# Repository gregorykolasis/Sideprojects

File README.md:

# Sideprojects
Some Python/Bat scripts for doing CD/CI operations , or scripts helping in deployment or general use scripts

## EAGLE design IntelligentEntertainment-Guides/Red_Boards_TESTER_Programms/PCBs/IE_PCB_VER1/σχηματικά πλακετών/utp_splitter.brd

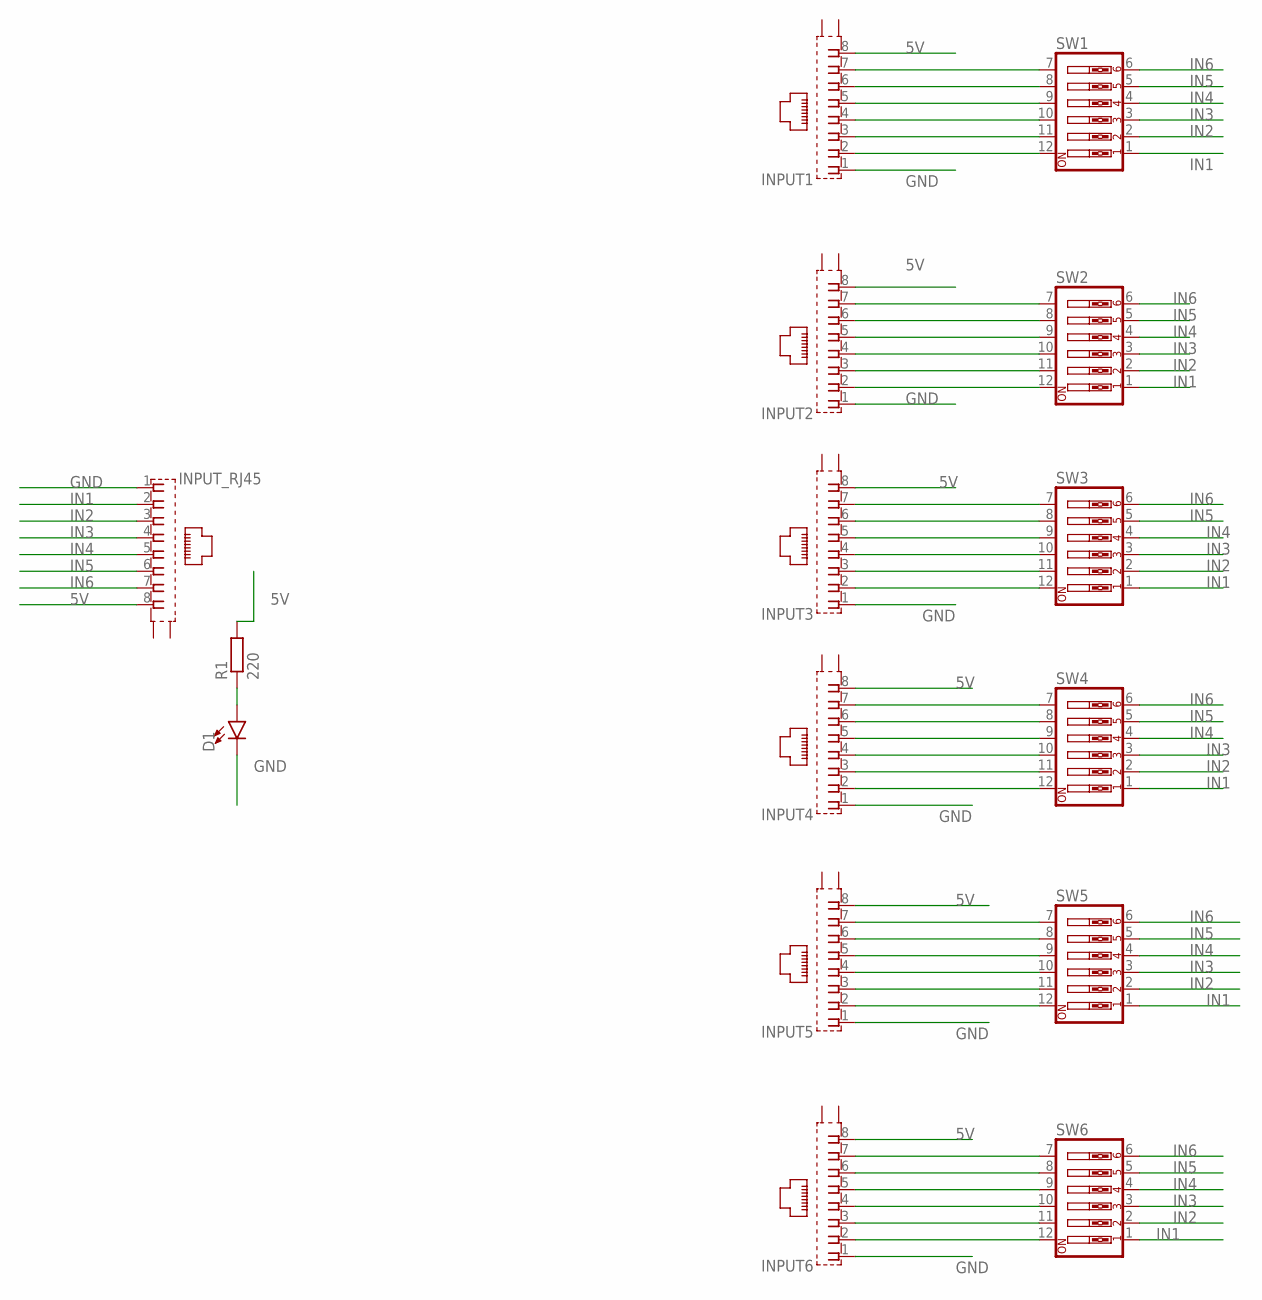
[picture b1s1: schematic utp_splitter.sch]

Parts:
D1: LED-5MM-KIT-NO-SILK; LED_5MM-KIT-NO-SILK
INPUT1, INPUT2, INPUT3, INPUT4, INPUT5, INPUT6: GLX-S-88M
INPUT_RJ45: GLX-S-88M
R1: 220; 0207/10
SW1, SW2, SW3, SW4, SW5, SW6: SW_DIP-6; EDG-06

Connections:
5V: INPUT1.8, INPUT2.8, INPUT3.8, INPUT4.8, INPUT5.8, INPUT6.8, INPUT_RJ45.8, R1.2
GND: D1.K (C), INPUT1.1, INPUT2.1, INPUT3.1, INPUT4.1, INPUT5.1, INPUT6.1, INPUT_RJ45.1
IN1: INPUT_RJ45.2, SW1.1, SW2.1, SW3.1, SW4.1, SW5.1, SW6.1
IN2: INPUT_RJ45.3, SW1.2, SW2.2, SW3.2, SW4.2, SW5.2, SW6.2
IN3: INPUT_RJ45.4, SW1.3, SW2.3, SW3.3, SW4.3, SW5.3, SW6.3
IN4: INPUT_RJ45.5, SW1.4, SW2.4, SW3.4, SW4.4, SW5.4, SW6.4
IN5: INPUT_RJ45.6, SW1.5, SW2.5, SW3.5, SW4.5, SW5.5, SW6.5
IN6: INPUT_RJ45.7, SW1.6, SW2.6, SW3.6, SW4.6, SW5.6, SW6.6
unnamed: INPUT6.7, SW6.7
unnamed: INPUT6.6, SW6.8
unnamed: INPUT6.5, SW6.9
unnamed: INPUT6.4, SW6.10
unnamed: INPUT6.3, SW6.11
unnamed: INPUT6.2, SW6.12
unnamed: D1.A, R1.1
unnamed: INPUT1.7, SW1.7
unnamed: INPUT1.6, SW1.8
unnamed: INPUT1.5, SW1.9
unnamed: INPUT1.4, SW1.10
unnamed: INPUT1.3, SW1.11
unnamed: INPUT1.2, SW1.12
unnamed: INPUT2.7, SW2.7
unnamed: INPUT2.6, SW2.8
unnamed: INPUT2.5, SW2.9
unnamed: INPUT2.4, SW2.10
unnamed: INPUT2.3, SW2.11
unnamed: INPUT2.2, SW2.12
unnamed: INPUT3.7, SW3.7
unnamed: INPUT3.6, SW3.8
unnamed: INPUT3.5, SW3.9
unnamed: INPUT3.4, SW3.10
unnamed: INPUT3.3, SW3.11
unnamed: INPUT3.2, SW3.12
unnamed: INPUT4.7, SW4.7
unnamed: INPUT4.6, SW4.8
unnamed: INPUT4.5, SW4.9
unnamed: INPUT4.4, SW4.10
unnamed: INPUT4.3, SW4.11
unnamed: INPUT4.2, SW4.12
unnamed: INPUT5.7, SW5.7
unnamed: INPUT5.6, SW5.8
unnamed: INPUT5.5, SW5.9
unnamed: INPUT5.4, SW5.10
unnamed: INPUT5.3, SW5.11
unnamed: INPUT5.2, SW5.12

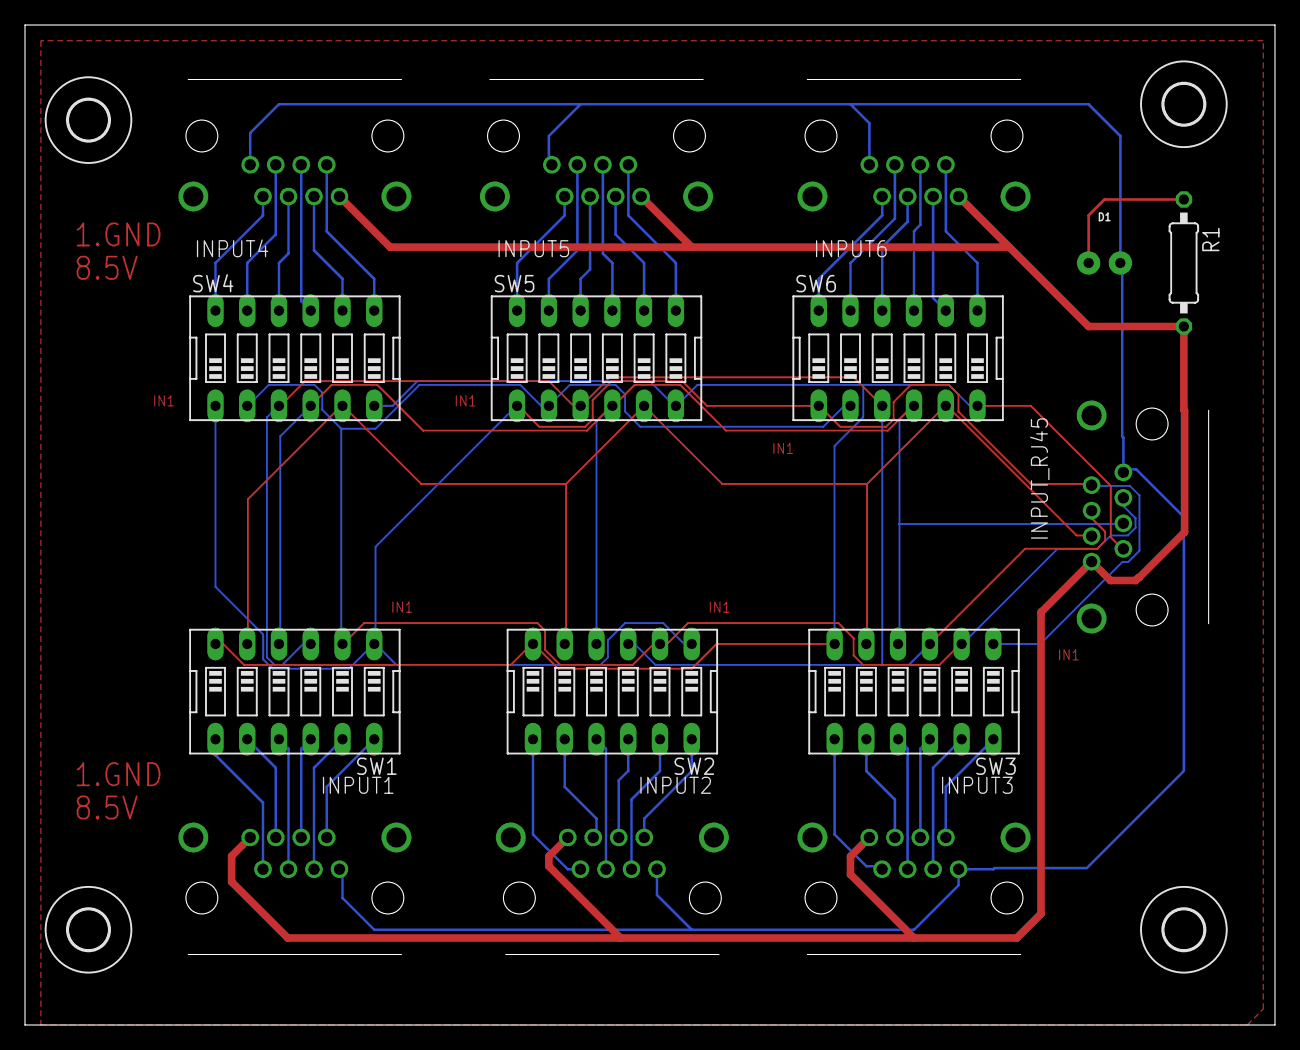
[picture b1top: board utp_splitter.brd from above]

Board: 2 copper layers, 100.0 x 80.0 mm, 19 parts (0 on the bottom side), 45 nets.

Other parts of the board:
U$1, U$2, U$3, U$4: 3,2

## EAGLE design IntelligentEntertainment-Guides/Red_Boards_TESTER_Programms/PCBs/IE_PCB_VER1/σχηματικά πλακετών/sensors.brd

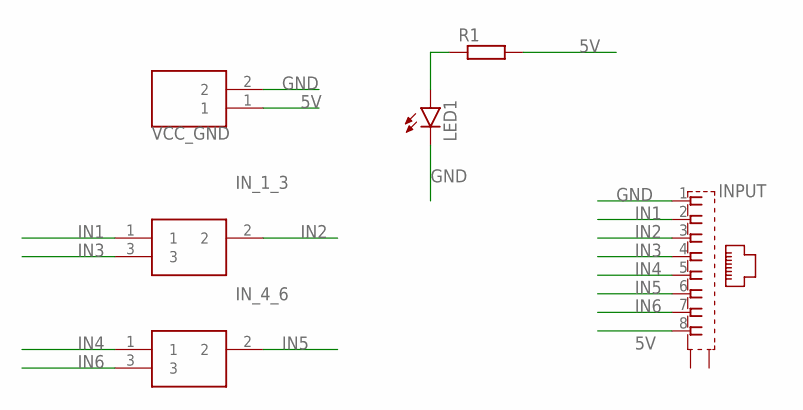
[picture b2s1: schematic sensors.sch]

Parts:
INPUT: GLX-S-88M
IN_1_3, IN_4_6: SAMACSYS_PARTS_TB006-508-03BE; SAMACSYS_PARTS_TB00650803BE
LED1: LED5MM
R1: R-EU_0207/10; 0207/10
VCC_GND: TB006-508-02BE_TB006-508-02BE; TB006-508-02BE_CUI_TB006-508-02BE

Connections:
5V: INPUT.8, R1.2, VCC_GND.1
GND: INPUT.1, LED1.K (C), VCC_GND.2
IN1: INPUT.2, IN_1_3.1
IN2: INPUT.3, IN_1_3.2
IN3: INPUT.4, IN_1_3.3
IN4: INPUT.5, IN_4_6.1
IN5: INPUT.6, IN_4_6.2
IN6: INPUT.7, IN_4_6.3
unnamed: LED1.A, R1.1

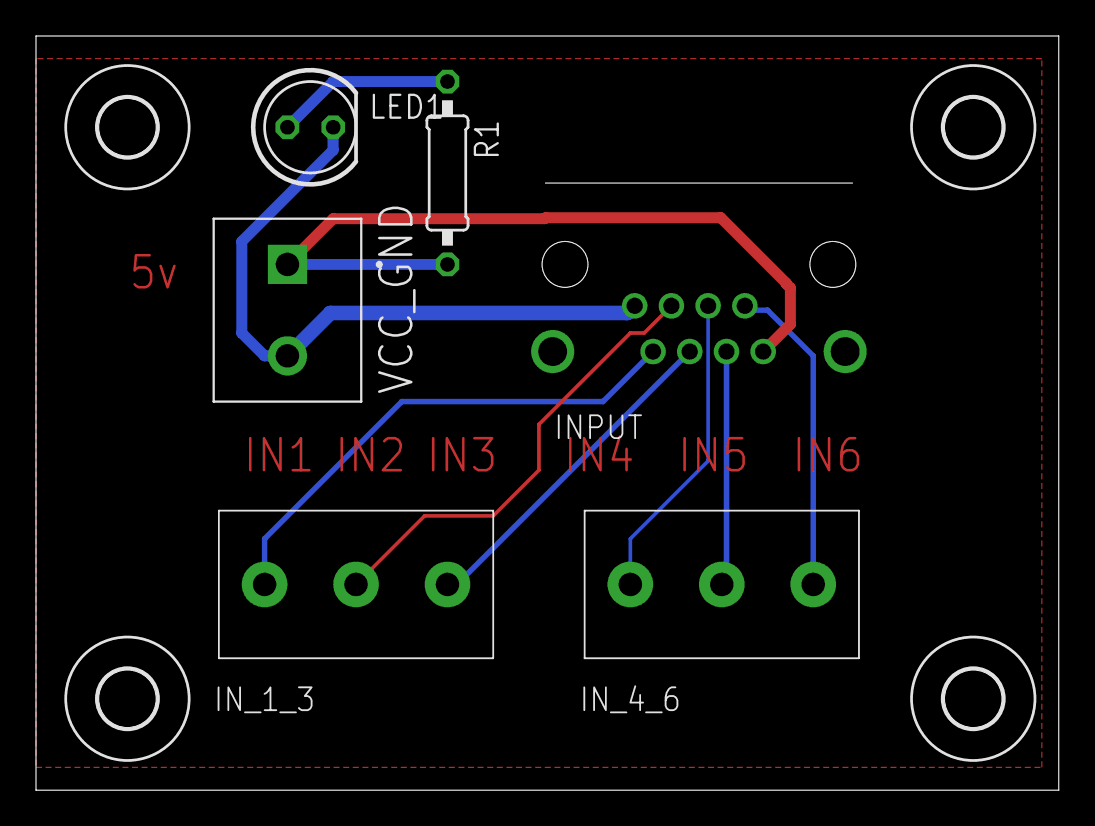
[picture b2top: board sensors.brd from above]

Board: 2 copper layers, 56.8 x 41.9 mm, 10 parts (0 on the bottom side), 9 nets.

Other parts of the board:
U$1, U$2, U$3, U$4: 3,2

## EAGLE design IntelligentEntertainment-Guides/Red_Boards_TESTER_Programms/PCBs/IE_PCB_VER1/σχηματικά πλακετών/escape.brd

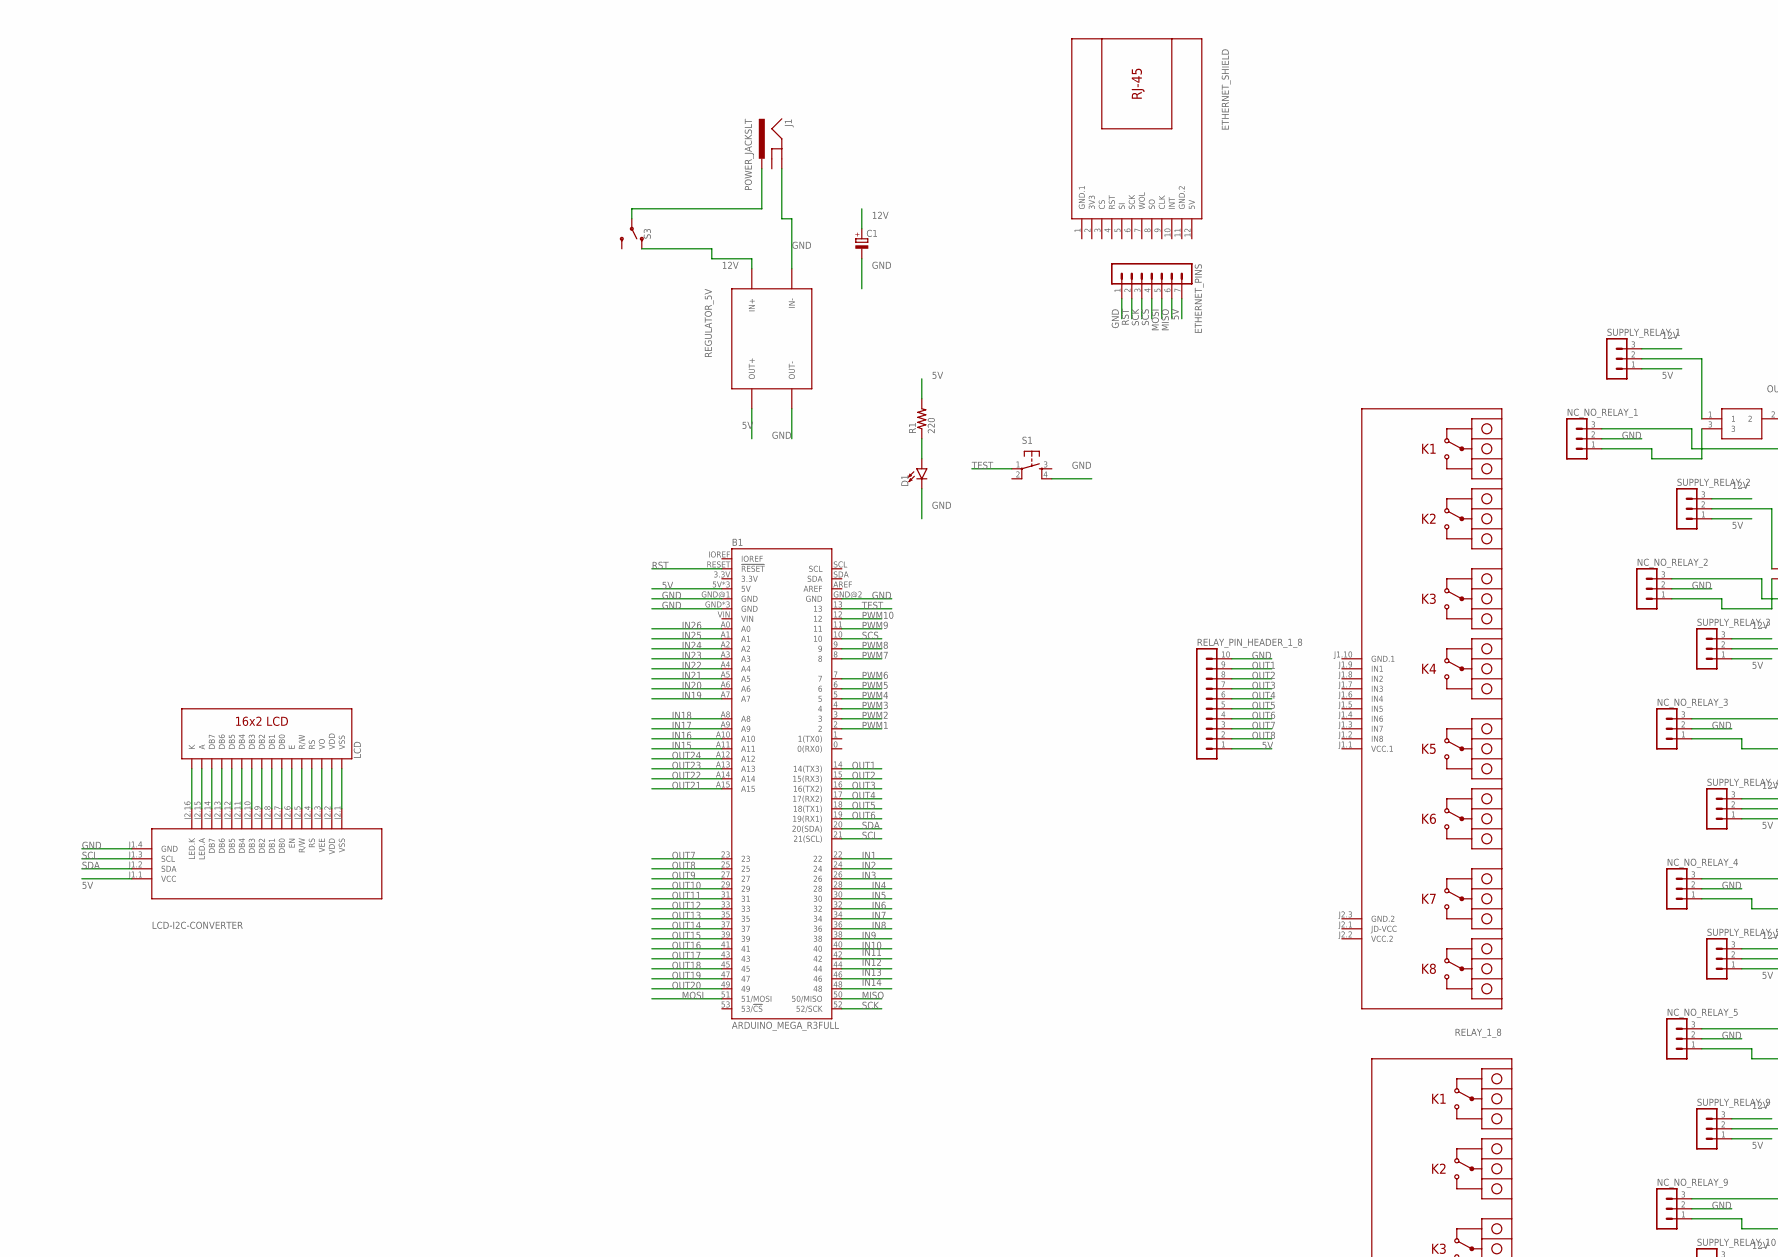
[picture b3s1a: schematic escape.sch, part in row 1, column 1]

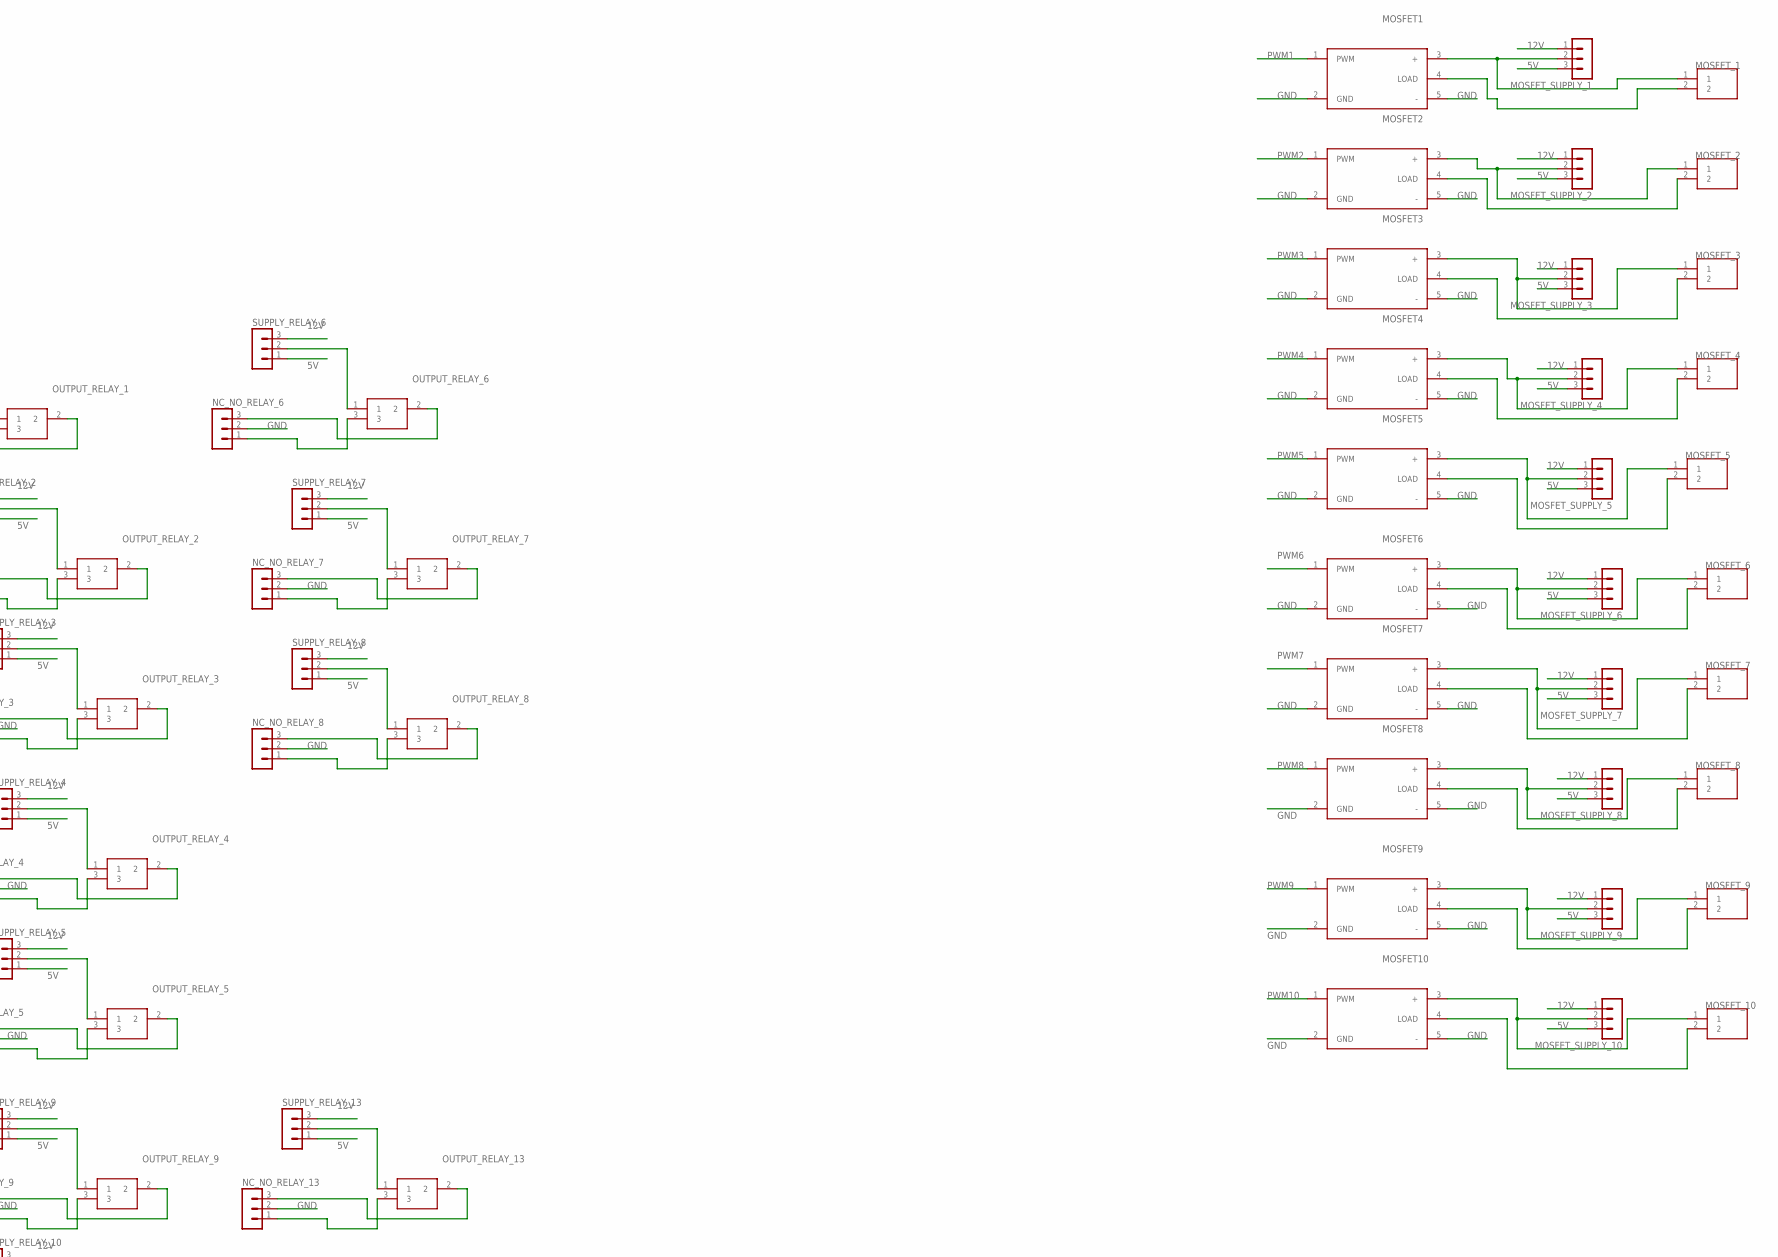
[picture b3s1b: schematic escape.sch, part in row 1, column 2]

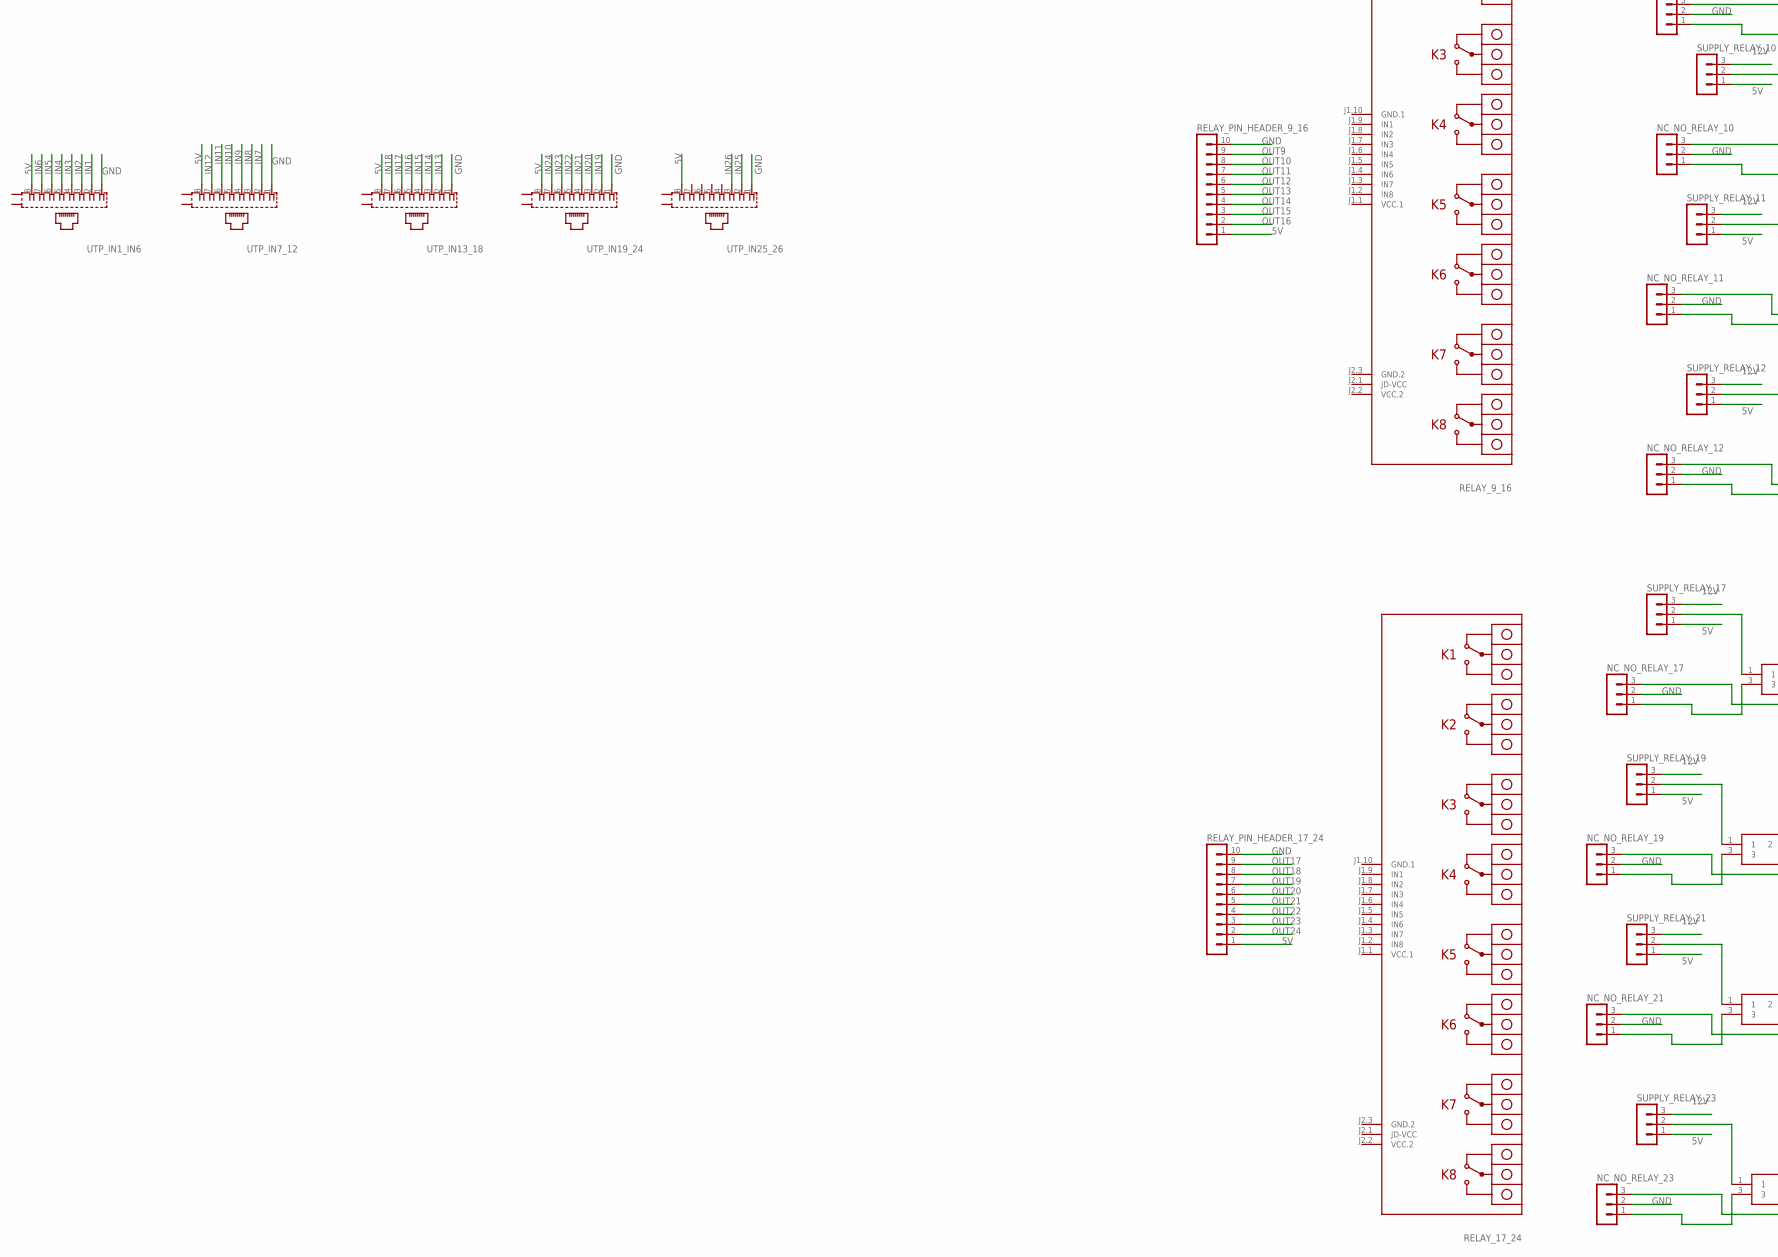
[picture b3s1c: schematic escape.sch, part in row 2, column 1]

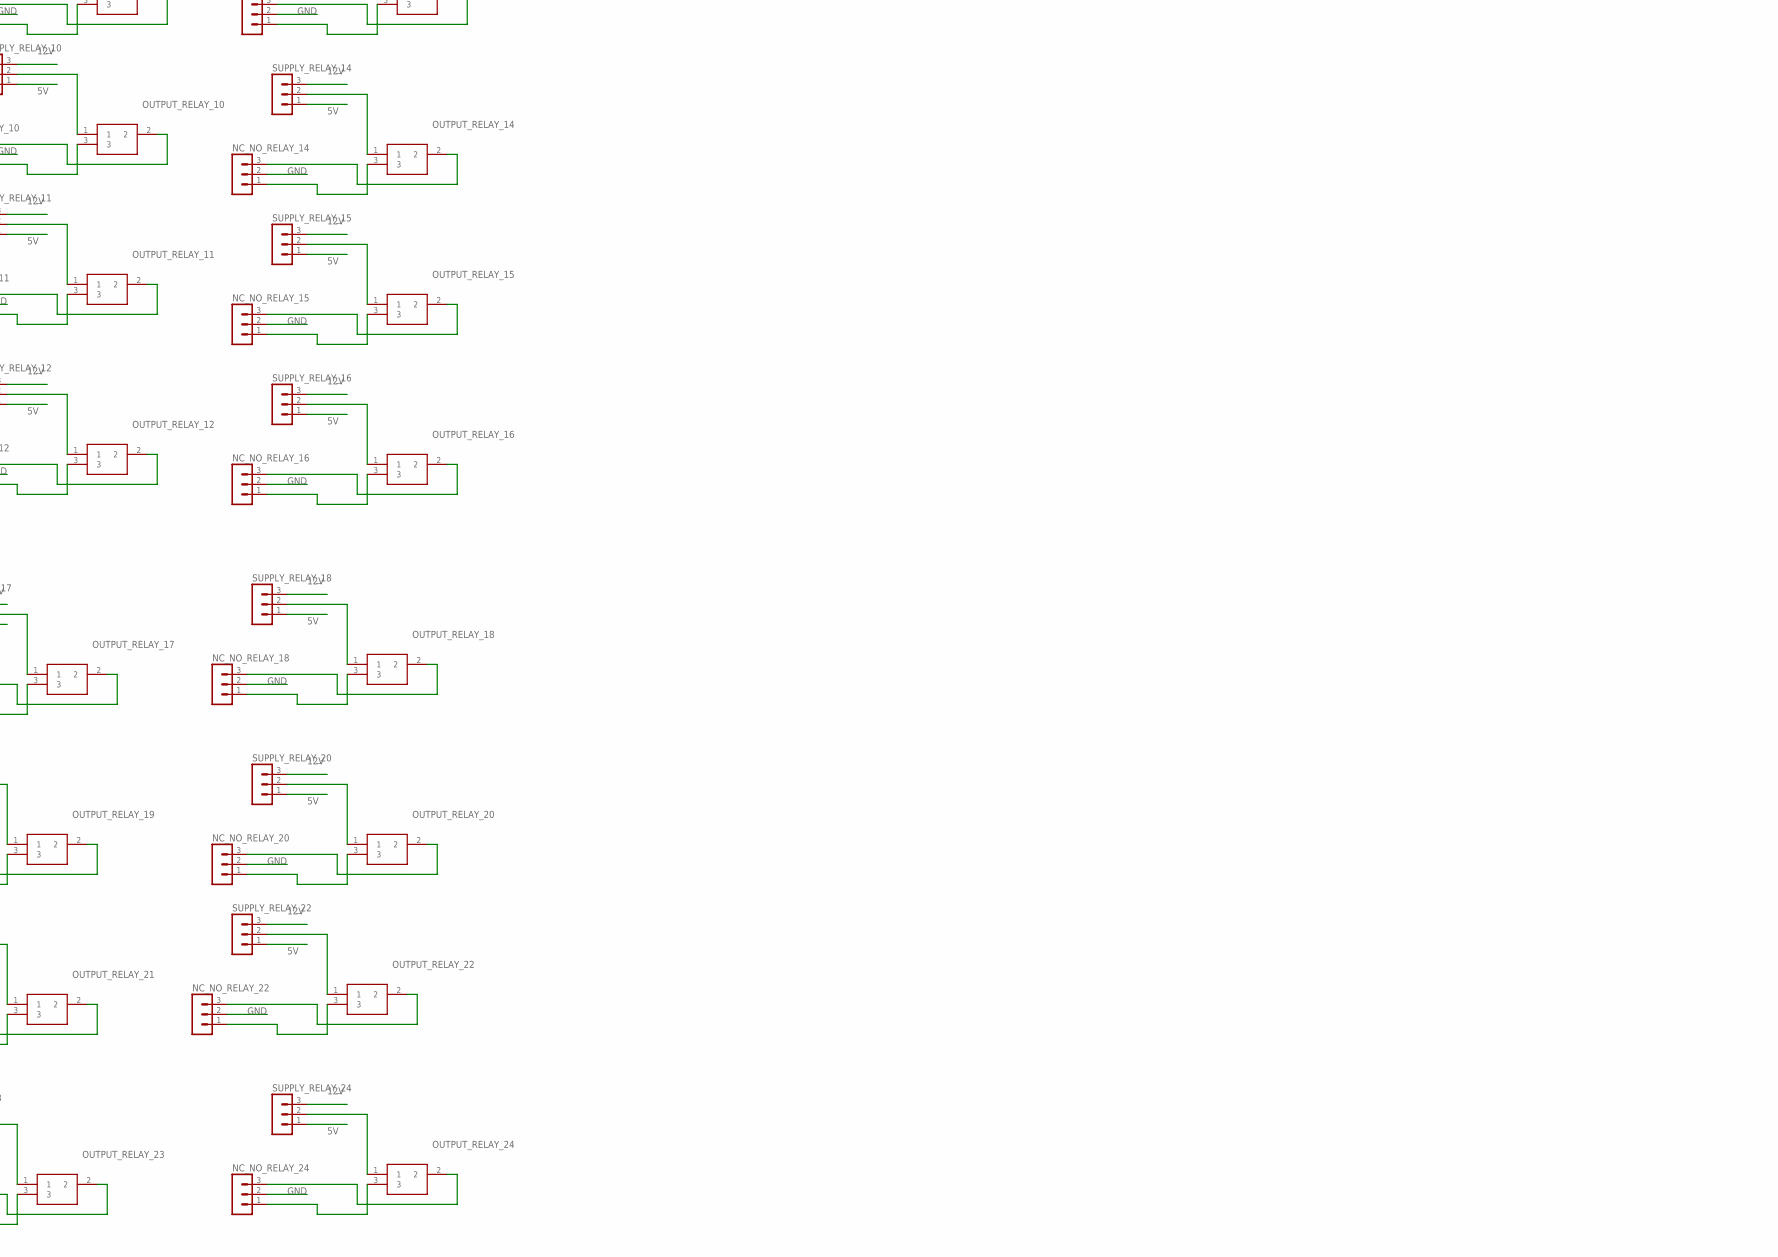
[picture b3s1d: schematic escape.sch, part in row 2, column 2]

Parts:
B1: ARDUINO_MEGA_R3FULL; ARDUINO_MEGA_NO_SILK
C1: CPOL-EUE3.5-10; E3,5-10
D1: LED5MM; LED_5MM
ETHERNET_PINS: MA07-1
ETHERNET_SHIELD: ETHERNET-ENC28J60
J1: POWER_JACKSLT; POWER_JACK_SLOT
LCD: LCD-16X2NOSILK; LCD-16X2_NOSILK
MOSFET1, MOSFET2, MOSFET3, MOSFET4, MOSFET5, MOSFET6, MOSFET7, MOSFET8, MOSFET9, MOSFET10: SAMACSYS_PARTS_FR120N-ISOLATED-MOSFET-MOD
MOSFET_1, MOSFET_2, MOSFET_3, MOSFET_4, MOSFET_5, MOSFET_6, MOSFET_7, MOSFET_8, MOSFET_9, MOSFET_10: TB006-508-02BE_TB006-508-02BE; TB006-508-02BE_CUI_TB006-508-02BE
MOSFET_SUPPLY_1, MOSFET_SUPPLY_2, MOSFET_SUPPLY_3, MOSFET_SUPPLY_4, MOSFET_SUPPLY_5, MOSFET_SUPPLY_6, MOSFET_SUPPLY_7, MOSFET_SUPPLY_8, MOSFET_SUPPLY_9, MOSFET_SUPPLY_10: MA03-1
NC_NO_RELAY_1, NC_NO_RELAY_2, NC_NO_RELAY_3, NC_NO_RELAY_4, NC_NO_RELAY_5, NC_NO_RELAY_6, NC_NO_RELAY_7, NC_NO_RELAY_8, NC_NO_RELAY_9, NC_NO_RELAY_10, NC_NO_RELAY_11, NC_NO_RELAY_12, NC_NO_RELAY_13, NC_NO_RELAY_14, NC_NO_RELAY_15, NC_NO_RELAY_16, NC_NO_RELAY_17, NC_NO_RELAY_18, NC_NO_RELAY_19, NC_NO_RELAY_20, NC_NO_RELAY_21, NC_NO_RELAY_22, NC_NO_RELAY_23, NC_NO_RELAY_24: MA03-1
OUTPUT_RELAY_1, OUTPUT_RELAY_2, OUTPUT_RELAY_3, OUTPUT_RELAY_4, OUTPUT_RELAY_5, OUTPUT_RELAY_6, OUTPUT_RELAY_7, OUTPUT_RELAY_8, OUTPUT_RELAY_9, OUTPUT_RELAY_10, OUTPUT_RELAY_11, OUTPUT_RELAY_12, OUTPUT_RELAY_13, OUTPUT_RELAY_14, OUTPUT_RELAY_15, OUTPUT_RELAY_16, OUTPUT_RELAY_17, OUTPUT_RELAY_18, OUTPUT_RELAY_19, OUTPUT_RELAY_20, OUTPUT_RELAY_21, OUTPUT_RELAY_22, OUTPUT_RELAY_23, OUTPUT_RELAY_24: SAMACSYS_PARTS_TB006-508-03BE; SAMACSYS_PARTS_TB00650803BE
R1: 220; 0207/10
REGULATOR_5V: DIY-MODULES_DC-DC-STEP-DOWN-LM2596
RELAY_1_8, RELAY_9_16, RELAY_17_24: RELAY-8-SRD
RELAY_PIN_HEADER_1_8, RELAY_PIN_HEADER_9_16, RELAY_PIN_HEADER_17_24: MA10-1
S1: TAC_SWITCHPTH; TACTILE-PTH
S3: SWITCH-SPDT-PTH-11.6X4.0MM-LOCK; SWITCH_SPDT_PTH_11.6X4.0MM_LOCK
SUPPLY_RELAY_1, SUPPLY_RELAY_2, SUPPLY_RELAY_3, SUPPLY_RELAY_4, SUPPLY_RELAY_5, SUPPLY_RELAY_6, SUPPLY_RELAY_7, SUPPLY_RELAY_8, SUPPLY_RELAY_9, SUPPLY_RELAY_10, SUPPLY_RELAY_11, SUPPLY_RELAY_12, SUPPLY_RELAY_13, SUPPLY_RELAY_14, SUPPLY_RELAY_15, SUPPLY_RELAY_16, SUPPLY_RELAY_17, SUPPLY_RELAY_18, SUPPLY_RELAY_19, SUPPLY_RELAY_20, SUPPLY_RELAY_21, SUPPLY_RELAY_22, SUPPLY_RELAY_23, SUPPLY_RELAY_24: MA03-1
U$3: LCD-I2C-CONVERTER
UTP_IN1_IN6, UTP_IN7_12, UTP_IN13_18, UTP_IN19_24, UTP_IN25_26: GLX-S-88M

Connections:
3V3: ETHERNET_SHIELD.2 (3V3)
5V: B1.5V, B1.5V@1 (5V), B1.5V@2 (5V), ETHERNET_PINS.7, ETHERNET_SHIELD.12 (5V), MOSFET_SUPPLY_1.3, MOSFET_SUPPLY_2.3, MOSFET_SUPPLY_3.3, MOSFET_SUPPLY_4.3, MOSFET_SUPPLY_5.3, MOSFET_SUPPLY_6.3, MOSFET_SUPPLY_7.3, MOSFET_SUPPLY_8.3, MOSFET_SUPPLY_9.3, MOSFET_SUPPLY_10.3, R1.2, REGULATOR_5V.OUT+, RELAY_PIN_HEADER_1_8.1, RELAY_PIN_HEADER_9_16.1, RELAY_PIN_HEADER_17_24.1, SUPPLY_RELAY_1.1, SUPPLY_RELAY_2.1, SUPPLY_RELAY_3.1, SUPPLY_RELAY_4.1, SUPPLY_RELAY_5.1, SUPPLY_RELAY_6.1, SUPPLY_RELAY_7.1, SUPPLY_RELAY_8.1, SUPPLY_RELAY_9.1, SUPPLY_RELAY_10.1, SUPPLY_RELAY_11.1, SUPPLY_RELAY_12.1, SUPPLY_RELAY_13.1, SUPPLY_RELAY_14.1, SUPPLY_RELAY_15.1, SUPPLY_RELAY_16.1, SUPPLY_RELAY_17.1, SUPPLY_RELAY_18.1, SUPPLY_RELAY_19.1, SUPPLY_RELAY_20.1, SUPPLY_RELAY_21.1, SUPPLY_RELAY_22.1, SUPPLY_RELAY_23.1, SUPPLY_RELAY_24.1, U$3.J1.1 (VCC), UTP_IN1_IN6.8, UTP_IN7_12.8, UTP_IN13_18.8, UTP_IN19_24.8, UTP_IN25_26.8
12V: C1.+, MOSFET_SUPPLY_1.1, MOSFET_SUPPLY_2.1, MOSFET_SUPPLY_3.1, MOSFET_SUPPLY_4.1, MOSFET_SUPPLY_5.1, MOSFET_SUPPLY_6.1, MOSFET_SUPPLY_7.1, MOSFET_SUPPLY_8.1, MOSFET_SUPPLY_9.1, MOSFET_SUPPLY_10.1, REGULATOR_5V.IN+, S3.1 (O), SUPPLY_RELAY_1.3, SUPPLY_RELAY_2.3, SUPPLY_RELAY_3.3, SUPPLY_RELAY_4.3, SUPPLY_RELAY_5.3, SUPPLY_RELAY_6.3, SUPPLY_RELAY_7.3, SUPPLY_RELAY_8.3, SUPPLY_RELAY_9.3, SUPPLY_RELAY_10.3, SUPPLY_RELAY_11.3, SUPPLY_RELAY_12.3, SUPPLY_RELAY_13.3, SUPPLY_RELAY_14.3, SUPPLY_RELAY_15.3, SUPPLY_RELAY_16.3, SUPPLY_RELAY_17.3, SUPPLY_RELAY_18.3, SUPPLY_RELAY_19.3, SUPPLY_RELAY_20.3, SUPPLY_RELAY_21.3, SUPPLY_RELAY_22.3, SUPPLY_RELAY_23.3, SUPPLY_RELAY_24.3
GND: B1.GND, B1.GND@1 (GND), B1.GND@2 (GND), B1.GND@3 (GND), B1.GND@4 (GND), C1.-, D1.K (C), ETHERNET_PINS.1, J1.GND@2 (GND), MOSFET1.2 (GND), MOSFET1.5 (-), MOSFET2.2 (GND), MOSFET2.5 (-), MOSFET3.2 (GND), MOSFET3.5 (-), MOSFET4.2 (GND), MOSFET4.5 (-), MOSFET5.2 (GND), MOSFET5.5 (-), MOSFET6.2 (GND), MOSFET6.5 (-), MOSFET7.2 (GND), MOSFET7.5 (-), MOSFET8.2 (GND), MOSFET8.5 (-), MOSFET9.2 (GND), MOSFET9.5 (-), MOSFET10.2 (GND), MOSFET10.5 (-), NC_NO_RELAY_1.2, NC_NO_RELAY_2.2, NC_NO_RELAY_3.2, NC_NO_RELAY_4.2, NC_NO_RELAY_5.2, NC_NO_RELAY_6.2, NC_NO_RELAY_7.2, NC_NO_RELAY_8.2, NC_NO_RELAY_9.2, NC_NO_RELAY_10.2, NC_NO_RELAY_11.2, NC_NO_RELAY_12.2, NC_NO_RELAY_13.2, NC_NO_RELAY_14.2, NC_NO_RELAY_15.2, NC_NO_RELAY_16.2, NC_NO_RELAY_17.2, NC_NO_RELAY_18.2, NC_NO_RELAY_19.2, NC_NO_RELAY_20.2, NC_NO_RELAY_21.2, NC_NO_RELAY_22.2, NC_NO_RELAY_23.2, NC_NO_RELAY_24.2, REGULATOR_5V.IN-, REGULATOR_5V.OUT-, RELAY_PIN_HEADER_1_8.10, RELAY_PIN_HEADER_9_16.10, RELAY_PIN_HEADER_17_24.10, S1.4, U$3.J1.4 (GND), UTP_IN1_IN6.1, UTP_IN7_12.1, UTP_IN13_18.1, UTP_IN19_24.1, UTP_IN25_26.1
GND.1: ETHERNET_SHIELD.1 (GND.1), RELAY_1_8.J1.10 (GND.1), RELAY_9_16.J1.10 (GND.1), RELAY_17_24.J1.10 (GND.1)
GND.2: ETHERNET_SHIELD.11 (GND.2), RELAY_1_8.J2.3 (GND.2), RELAY_9_16.J2.3 (GND.2), RELAY_17_24.J2.3 (GND.2)
IN1: B1.22, UTP_IN1_IN6.2
IN2: B1.24, UTP_IN1_IN6.3
IN3: B1.26, UTP_IN1_IN6.4
IN4: B1.28, UTP_IN1_IN6.5
IN5: B1.30, UTP_IN1_IN6.6
IN6: B1.32, UTP_IN1_IN6.7
IN7: B1.34, UTP_IN7_12.2
IN8: B1.36, UTP_IN7_12.3
IN9: B1.38, UTP_IN7_12.4
IN10: B1.40, UTP_IN7_12.5
IN11: B1.42, UTP_IN7_12.6
IN12: B1.44, UTP_IN7_12.7
IN13: B1.46, UTP_IN13_18.2
IN14: B1.48, UTP_IN13_18.3
IN15: B1.A11, UTP_IN13_18.4
IN16: B1.A10, UTP_IN13_18.5
IN17: B1.A9, UTP_IN13_18.6
IN18: B1.A8, UTP_IN13_18.7
IN19: B1.A7, UTP_IN19_24.2
IN20: B1.A6, UTP_IN19_24.3
IN21: B1.A5, UTP_IN19_24.4
IN22: B1.A4, UTP_IN19_24.5
IN23: B1.A3, UTP_IN19_24.6
IN24: B1.A2, UTP_IN19_24.7
IN25: B1.A1, UTP_IN25_26.2
IN26: B1.A0, UTP_IN25_26.3
MISO: B1.50 (50/MISO), ETHERNET_PINS.6
MOSI: B1.51 (51/MOSI), ETHERNET_PINS.5
unnamed: OUTPUT_RELAY_1.1, SUPPLY_RELAY_1.2
unnamed: D1.A, R1.1
unnamed: OUTPUT_RELAY_2.1, SUPPLY_RELAY_2.2
unnamed: NC_NO_RELAY_1.3, OUTPUT_RELAY_1.2
unnamed: NC_NO_RELAY_1.1, OUTPUT_RELAY_1.3
unnamed: NC_NO_RELAY_2.3, OUTPUT_RELAY_2.2
unnamed: NC_NO_RELAY_2.1, OUTPUT_RELAY_2.3
unnamed: OUTPUT_RELAY_3.1, SUPPLY_RELAY_3.2
unnamed: NC_NO_RELAY_3.3, OUTPUT_RELAY_3.2
unnamed: NC_NO_RELAY_3.1, OUTPUT_RELAY_3.3
unnamed: LCD.16 (K), U$3.J2.16 (LED.K)
unnamed: LCD.15 (A), U$3.J2.15 (LED.A)
unnamed: LCD.14 (DB7), U$3.J2.14 (DB7)
unnamed: LCD.13 (DB6), U$3.J2.13 (DB6)
unnamed: LCD.12 (DB5), U$3.J2.12 (DB5)
unnamed: LCD.11 (DB4), U$3.J2.11 (DB4)
unnamed: LCD.10 (DB3), U$3.J2.10 (DB3)
unnamed: LCD.9 (DB2), U$3.J2.9 (DB2)
unnamed: LCD.8 (DB1), U$3.J2.8 (DB1)
unnamed: LCD.7 (DB0), U$3.J2.7 (DB0)
unnamed: LCD.6 (E), U$3.J2.6 (EN)
unnamed: LCD.5 (R/W), U$3.J2.5 (R/W)
unnamed: LCD.4 (RS), U$3.J2.4 (RS)
unnamed: LCD.3 (VO), U$3.J2.3 (VEE)
unnamed: LCD.2 (VDD), U$3.J2.2 (VDD)
unnamed: LCD.1 (VSS), U$3.J2.1 (VSS)
unnamed: OUTPUT_RELAY_9.1, SUPPLY_RELAY_9.2
unnamed: OUTPUT_RELAY_4.1, SUPPLY_RELAY_4.2
unnamed: NC_NO_RELAY_9.3, OUTPUT_RELAY_9.2
unnamed: NC_NO_RELAY_4.3, OUTPUT_RELAY_4.2
unnamed: NC_NO_RELAY_4.1, OUTPUT_RELAY_4.3
unnamed: OUTPUT_RELAY_5.1, SUPPLY_RELAY_5.2
unnamed: NC_NO_RELAY_9.1, OUTPUT_RELAY_9.3
unnamed: NC_NO_RELAY_5.3, OUTPUT_RELAY_5.2
unnamed: OUTPUT_RELAY_10.1, SUPPLY_RELAY_10.2
unnamed: NC_NO_RELAY_5.1, OUTPUT_RELAY_5.3
unnamed: OUTPUT_RELAY_6.1, SUPPLY_RELAY_6.2
unnamed: NC_NO_RELAY_6.3, OUTPUT_RELAY_6.2
unnamed: NC_NO_RELAY_10.3, OUTPUT_RELAY_10.2
unnamed: NC_NO_RELAY_6.1, OUTPUT_RELAY_6.3
unnamed: NC_NO_RELAY_10.1, OUTPUT_RELAY_10.3
unnamed: OUTPUT_RELAY_7.1, SUPPLY_RELAY_7.2
unnamed: NC_NO_RELAY_7.3, OUTPUT_RELAY_7.2
unnamed: OUTPUT_RELAY_11.1, SUPPLY_RELAY_11.2
unnamed: NC_NO_RELAY_11.3, OUTPUT_RELAY_11.2
unnamed: NC_NO_RELAY_7.1, OUTPUT_RELAY_7.3
unnamed: OUTPUT_RELAY_8.1, SUPPLY_RELAY_8.2
unnamed: NC_NO_RELAY_8.3, OUTPUT_RELAY_8.2
unnamed: NC_NO_RELAY_11.1, OUTPUT_RELAY_11.3
unnamed: NC_NO_RELAY_8.1, OUTPUT_RELAY_8.3
unnamed: MOSFET1.3 (+), MOSFET_1.1, MOSFET_SUPPLY_1.2
unnamed: MOSFET1.4 (LOAD), MOSFET_1.2
unnamed: MOSFET2.3 (+), MOSFET_2.1, MOSFET_SUPPLY_2.2
unnamed: MOSFET2.4 (LOAD), MOSFET_2.2
unnamed: MOSFET3.3 (+), MOSFET_3.1, MOSFET_SUPPLY_3.2
unnamed: MOSFET3.4 (LOAD), MOSFET_3.2
unnamed: MOSFET4.3 (+), MOSFET_4.1, MOSFET_SUPPLY_4.2
unnamed: OUTPUT_RELAY_12.1, SUPPLY_RELAY_12.2
unnamed: MOSFET4.4 (LOAD), MOSFET_4.2
unnamed: NC_NO_RELAY_12.3, OUTPUT_RELAY_12.2
unnamed: NC_NO_RELAY_12.1, OUTPUT_RELAY_12.3
unnamed: MOSFET5.3 (+), MOSFET_5.1, MOSFET_SUPPLY_5.2
unnamed: OUTPUT_RELAY_13.1, SUPPLY_RELAY_13.2
unnamed: NC_NO_RELAY_13.3, OUTPUT_RELAY_13.2
unnamed: MOSFET5.4 (LOAD), MOSFET_5.2
unnamed: NC_NO_RELAY_13.1, OUTPUT_RELAY_13.3
unnamed: OUTPUT_RELAY_14.1, SUPPLY_RELAY_14.2
unnamed: MOSFET6.3 (+), MOSFET_6.1, MOSFET_SUPPLY_6.2
unnamed: NC_NO_RELAY_14.3, OUTPUT_RELAY_14.2
unnamed: NC_NO_RELAY_14.1, OUTPUT_RELAY_14.3
unnamed: MOSFET6.4 (LOAD), MOSFET_6.2
unnamed: OUTPUT_RELAY_15.1, SUPPLY_RELAY_15.2
unnamed: NC_NO_RELAY_15.3, OUTPUT_RELAY_15.2
unnamed: MOSFET7.3 (+), MOSFET_7.1, MOSFET_SUPPLY_7.2
unnamed: MOSFET7.4 (LOAD), MOSFET_7.2
unnamed: MOSFET8.3 (+), MOSFET_8.1, MOSFET_SUPPLY_8.2
unnamed: MOSFET8.4 (LOAD), MOSFET_8.2
unnamed: MOSFET9.3 (+), MOSFET_9.1, MOSFET_SUPPLY_9.2
unnamed: MOSFET9.4 (LOAD), MOSFET_9.2
unnamed: MOSFET10.3 (+), MOSFET_10.1, MOSFET_SUPPLY_10.2
unnamed: MOSFET10.4 (LOAD), MOSFET_10.2
unnamed: NC_NO_RELAY_15.1, OUTPUT_RELAY_15.3
unnamed: OUTPUT_RELAY_16.1, SUPPLY_RELAY_16.2
unnamed: NC_NO_RELAY_16.3, OUTPUT_RELAY_16.2
unnamed: NC_NO_RELAY_16.1, OUTPUT_RELAY_16.3
unnamed: OUTPUT_RELAY_17.1, SUPPLY_RELAY_17.2
unnamed: NC_NO_RELAY_17.3, OUTPUT_RELAY_17.2
unnamed: NC_NO_RELAY_17.1, OUTPUT_RELAY_17.3
unnamed: OUTPUT_RELAY_18.1, SUPPLY_RELAY_18.2
unnamed: NC_NO_RELAY_18.3, OUTPUT_RELAY_18.2
unnamed: NC_NO_RELAY_18.1, OUTPUT_RELAY_18.3
unnamed: OUTPUT_RELAY_19.1, SUPPLY_RELAY_19.2
unnamed: NC_NO_RELAY_19.3, OUTPUT_RELAY_19.2
unnamed: NC_NO_RELAY_19.1, OUTPUT_RELAY_19.3
unnamed: OUTPUT_RELAY_20.1, SUPPLY_RELAY_20.2
unnamed: NC_NO_RELAY_20.3, OUTPUT_RELAY_20.2
unnamed: NC_NO_RELAY_20.1, OUTPUT_RELAY_20.3
unnamed: OUTPUT_RELAY_21.1, SUPPLY_RELAY_21.2
unnamed: NC_NO_RELAY_21.3, OUTPUT_RELAY_21.2
unnamed: NC_NO_RELAY_21.1, OUTPUT_RELAY_21.3
unnamed: OUTPUT_RELAY_22.1, SUPPLY_RELAY_22.2
unnamed: NC_NO_RELAY_22.3, OUTPUT_RELAY_22.2
unnamed: NC_NO_RELAY_22.1, OUTPUT_RELAY_22.3
unnamed: OUTPUT_RELAY_23.1, SUPPLY_RELAY_23.2
unnamed: NC_NO_RELAY_23.3, OUTPUT_RELAY_23.2
unnamed: NC_NO_RELAY_23.1, OUTPUT_RELAY_23.3
unnamed: OUTPUT_RELAY_24.1, SUPPLY_RELAY_24.2
unnamed: NC_NO_RELAY_24.3, OUTPUT_RELAY_24.2
unnamed: NC_NO_RELAY_24.1, OUTPUT_RELAY_24.3
unnamed: J1.PWR, S3.2
OUT1: B1.14 (14(TX3)), RELAY_PIN_HEADER_1_8.9
OUT2: B1.15 (15(RX3)), RELAY_PIN_HEADER_1_8.8
OUT3: B1.16 (16(TX2)), RELAY_PIN_HEADER_1_8.7
OUT4: B1.17 (17(RX2)), RELAY_PIN_HEADER_1_8.6
OUT5: B1.18 (18(TX1)), RELAY_PIN_HEADER_1_8.5
OUT6: B1.19 (19(RX1)), RELAY_PIN_HEADER_1_8.4
OUT7: B1.23, RELAY_PIN_HEADER_1_8.3
OUT8: B1.25, RELAY_PIN_HEADER_1_8.2
OUT9: B1.27, RELAY_PIN_HEADER_9_16.9
OUT10: B1.29, RELAY_PIN_HEADER_9_16.8
OUT11: B1.31, RELAY_PIN_HEADER_9_16.7
OUT12: B1.33, RELAY_PIN_HEADER_9_16.6
OUT13: B1.35, RELAY_PIN_HEADER_9_16.5
OUT14: B1.37, RELAY_PIN_HEADER_9_16.4
OUT15: B1.39, RELAY_PIN_HEADER_9_16.3
OUT16: B1.41, RELAY_PIN_HEADER_9_16.2
OUT17: B1.43, RELAY_PIN_HEADER_17_24.9
OUT18: B1.45, RELAY_PIN_HEADER_17_24.8
OUT19: B1.47, RELAY_PIN_HEADER_17_24.7
OUT20: B1.49, RELAY_PIN_HEADER_17_24.6
OUT21: B1.A15, RELAY_PIN_HEADER_17_24.5
OUT22: B1.A14, RELAY_PIN_HEADER_17_24.4
OUT23: B1.A13, RELAY_PIN_HEADER_17_24.3
OUT24: B1.A12, RELAY_PIN_HEADER_17_24.2
PWM1: B1.2, MOSFET1.1 (PWM)
PWM2: B1.3, MOSFET2.1 (PWM)
PWM3: B1.4, MOSFET3.1 (PWM)
PWM4: B1.5, MOSFET4.1 (PWM)
PWM5: B1.6, MOSFET5.1 (PWM)
PWM6: B1.7, MOSFET6.1 (PWM)
PWM7: B1.8, MOSFET7.1 (PWM)
PWM8: B1.9, MOSFET8.1 (PWM)
PWM9: B1.11, MOSFET9.1 (PWM)
PWM10: B1.12, MOSFET10.1 (PWM)
RST: B1.RESET (!RESET), ETHERNET_PINS.2
SCK: B1.52 (52/SCK), ETHERNET_PINS.3
SCL: B1.21 (21(SCL)), U$3.J1.3 (SCL)
SCS: B1.10, ETHERNET_PINS.4
SDA: B1.20 (20(SDA)), U$3.J1.2 (SDA)
TEST: B1.13, S1.1
VCC.1: RELAY_1_8.J1.1 (VCC.1), RELAY_9_16.J1.1 (VCC.1), RELAY_17_24.J1.1 (VCC.1)
VCC.2: RELAY_1_8.J2.2 (VCC.2), RELAY_9_16.J2.2 (VCC.2), RELAY_17_24.J2.2 (VCC.2)

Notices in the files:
parts and their libraries:
SparkFun-Boards: Licensing: Creative Commons ShareAlike 4.0 International - https://creativecommons.org/licenses/by-sa/4.0
diy-modules: Released under the Creative Commons Attribution 4.0 International License: http://creativecommons.org/licenses/by/4.0
